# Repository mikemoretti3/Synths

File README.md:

This is my synth design repo.  It includes schematics, board files, and notes for some of the synth designs I've made/borrowed.  Some of these come from Electronotes, MFOS, and elsewhere.  There are also my own designs (under the mordent directory).

The files in this repo were made using Eagle 6.5 (and there is a library file I use in here too).

In general, I prefer flying wire panel component wiring.  I have one pad for GNDPNL which I use to ground all my panel components that need ground.  I connect that pad to one component and then string the rest off each other from there.  Also, make note of pot-pinout.jpg.  That is how I wire pretty much all my pots.  Some of the Electronotes ones may be backward (because I messed up the ordering or they just did it in reverse; I've seen this on VCF frequency/resonance pots from different vendors; some turn clockwise for higher resonance, etc and some turn anti-clockwise).

Don't build VCO1.  I have to look at my module and take a picture and figure out some resistor changes.  I probably shouldn't have included that one yet (I plan to redo that board at some point).

The VEWA can be built as separate modules (this is my preferred way to build it).  There is an LFO board and a filter board.  For the filter board I put jacks in for the 3 frequency CVs  (one for each of the formant filters), the notch, and the Q.  This module is wired for +/-15v.  If you have +/-12 look at the jpg for that.  It's ok to use 100k pots instead of 200k.  There are lines marked A though H, only 5 of which have pads, here is what they mean (ignore the fact that they say "to switches" unless you want to combine the lfo board with it):
C,D,E - are input jacks for freq modulation for the 1st-3rd formant  filters
G - is an input jack for the notch filter frequency CV modulation
H - is an input jack for Q (resonance) CV modulation (Q anim),  (internally it's attached to pin 1 of the Q anim pot, this gets fed into the Q summer which outputs to line B)
There are a total of 7 jacks (in, out, and 5 cv modulation inputs).
You can ignore +15VBB, -15VBB, and GNDBB, they were board to board power  for the LFO board that went with the dual board version and aren't connected.  GNDPNL is the ground I use for all the panel wiring and I run ground wires from panel component to panel component.

Most of the rest of the boards are set to run off +/-12v.  +/-15v should be fine although some of the audio signals may be > +/-5v.

The EchoFX is straight from Music From Outer Space; design notes are there.

The Electronotes ones are documented in the EN pdf files.

Under the "mordent" folder, I have my own drum module design based on some electronotes filters, noise, vcos, and ring modulators.  It's very modular and you can probably stripboard or chop out individual parts of it (i.e. noise + filter + env; vco + env; vco + vco + ringmod).  It's pretty straightforward from the board layout and schematic.  There's also a little mixer and mult board.

There's a util-vco that I use a LOT to test new designs with.  I have 12v and 15v versions of this built that I use as a VCO for input to something or an LFO (it has a huge range).  It's not super accurate, but for using it as a test unit it's perfect.

If you have any questions at all please feel free to contact me via github.

Enjoy!
 
Mike Moretti
http://mordent.com
♩♫♫♩♪♩

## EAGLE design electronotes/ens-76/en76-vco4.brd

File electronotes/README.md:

Electronotes modules
Eurorack and other formats

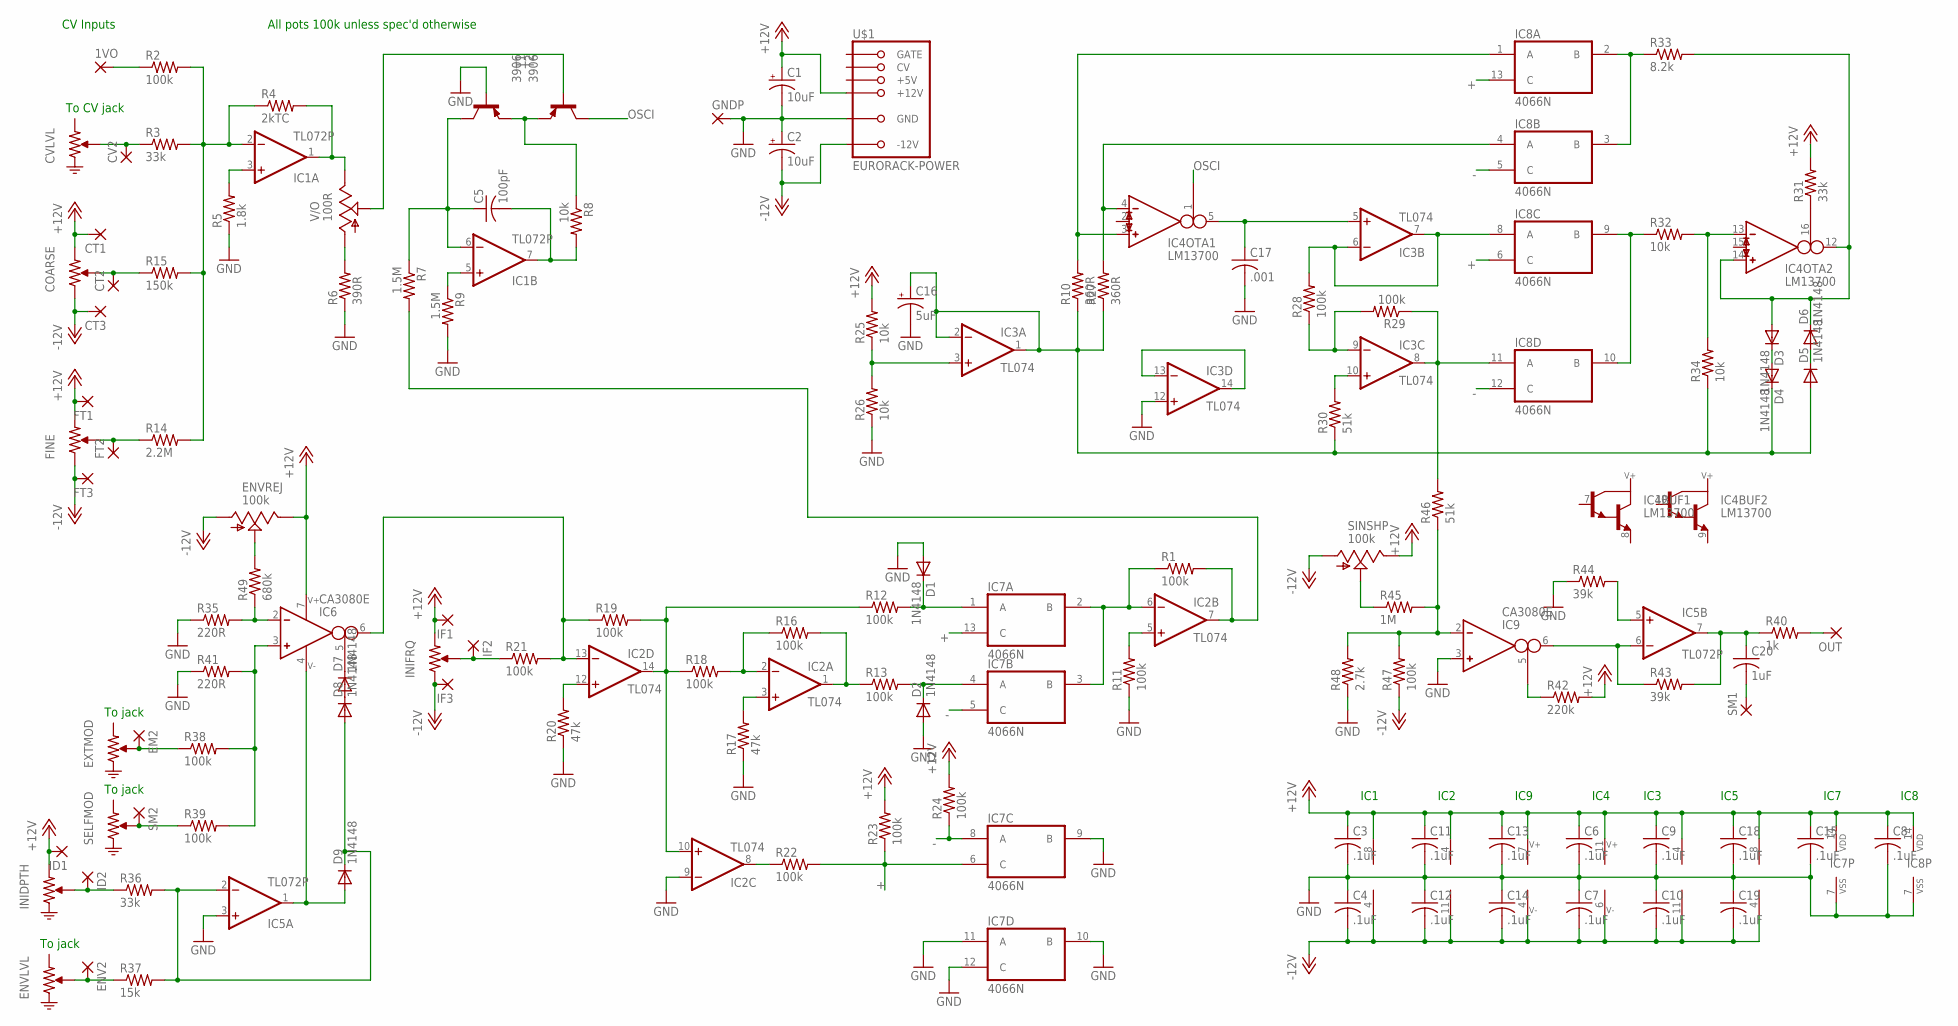
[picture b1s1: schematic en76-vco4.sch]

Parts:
1VO: 2,54/1,0
C1, C2: 10uF; E2-5
C3, C4, C6, C7, C8, C9, C10, C11, C12, C13, C14, C15, C18, C19: .1uF; C050-025X075
C5: 100pF; C050-025X075
C16: 5uF; E2-5
C17: .001; C050-025X075
C20: 1uF; C050-025X075
CT1, CT2, CT3: 2,54/1,0
CV2: 2,54/1,0
D1, D2, D3, D4, D5, D6, D7, D8, D9: 1N4148; DO35-7
EM2: 2,54/1,0
ENV2: 2,54/1,0
ENVREJ: 100k; RJ9W
FT1, FT2, FT3: 2,54/1,0
GNDP: 2,54/1,0
IC1, IC5: TL072P; DIL08
IC2, IC3: TL074; DIL14
IC4: LM13700; DIL16
IC6, IC9: CA3080E; DIL08
IC7, IC8: 4066N; DIL14
ID1, ID2: 2,54/1,0
IF1, IF2, IF3: 2,54/1,0
OUT: 2,54/1,0
R1, R2, R11, R12, R13, R16, R18, R19, R21, R22, R23, R24, R28, R29, R38, R39, R47: 100k; 0207/10
R3, R31, R36: 33k; 0207/10
R4: 2kTC; 0207/10
R5: 1.8k; 0207/10
R6: 390R; 0207/10
R7, R9: 1.5M; 0207/10
R8, R25, R26, R32, R34: 10k; 0207/10
R10, R27: 360R; 0207/10
R14: 2.2M; 0207/10
R15: 150k; 0207/10
R17, R20: 47k; 0207/10
R30, R46: 51k; 0207/10
R33: 8.2k; 0207/10
R35, R41: 220R; 0207/10
R37: 15k; 0207/10
R40: 1k; 0207/10
R42: 220k; 0207/10
R43, R44: 39k; 0207/10
R45: 1M; 0207/10
R48: 2.7k; 0207/10
R49: 680k; 0207/10
SINSHP: 100k; RJ9W
SM1, SM2: 2,54/1,0
T1, T2: 3906; TO92-EBC
U$1: EURORACK-POWER; PINSHRD_PTH_2X8
V/O: 100R; RJ9W

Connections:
+: IC7.6 (C), IC7.13 (C), IC8.6 (C), IC8.13 (C), R22.2, R23.1
+12V: C1.+, C3.1, C6.1, C8.1, C9.1, C11.1, C13.1, C15.1, C18.1, CT1.1, ENVREJ.E, FT1.1, IC1.8 (V+), IC2.4 (V+), IC3.4 (V+), IC4.11 (7), IC5.8 (V+), IC6.7, IC7.14 (VDD), IC8.14 (VDD), IC9.7, ID1.1, IF1.1, R23.2, R24.2, R25.2, R31.2, R42.2, SINSHP.E, U$1.+12V@1 (+12V), U$1.+12V@2 (+12V)
-: IC7.5 (C), IC7.8 (A), IC8.5 (C), IC8.12 (C), R24.1
-12V: C2.-, C4.2, C7.2, C10.2, C12.2, C14.2, C19.2, CT3.1, ENVREJ.A, FT3.1, IC1.4 (V-), IC2.11 (V-), IC3.11 (V-), IC4.6 (4), IC5.4 (V-), IC9.4, IF3.1, R47.1, SINSHP.A, U$1.-12V@1 (-12V), U$1.-12V@2 (-12V)
GND: C1.-, C2.+, C3.2, C4.1, C6.2, C7.1, C8.2, C9.2, C10.1, C11.2, C12.1, C13.2, C14.1, C15.2, C16.-, C17.2, C18.2, C19.1, D1.A, D2.A, GNDP.1, IC2.9 (-IN), IC3.12 (+IN), IC5.3 (+IN), IC7.7 (VSS), IC7.9 (B), IC7.10 (B), IC7.11 (A), IC7.12 (C), IC8.7 (VSS), IC9.3 (IN_P), R5.1, R6.1, R9.2, R11.1, R17.1, R20.1, R26.1, R35.1, R41.1, R44.1, R48.1, T2.B, U$1.GND@1 (GND), U$1.GND@2 (GND), U$1.GND@3 (GND), U$1.GND@4 (GND), U$1.GND@5 (GND), U$1.GND@6 (GND)
unnamed: CT2.1, R15.1
unnamed: CV2.1, R3.1
unnamed: 1VO.1, R2.1
unnamed: T1.B, V/O.S
unnamed: IC1.3 (+IN), R5.2
unnamed: IC1.2 (-IN), R2.2, R3.2, R4.1, R14.2, R15.2
unnamed: IC1.1 (OUT), R4.2, V/O.E
unnamed: R6.2, V/O.A
unnamed: C5.1, IC1.6 (-IN), R7.1, T2.C
unnamed: R8.1, T1.E, T2.E
unnamed: C5.2, IC1.7 (OUT), R8.2
unnamed: FT2.1, R14.1
unnamed: IC4.3 (IN_P), IC8.1 (A), R10.2
unnamed: IC1.5 (+IN), R9.1
unnamed: IC2.6 (-IN), IC7.2 (B), IC7.3 (B), R1.1
unnamed: IC2.5 (+IN), R11.2
unnamed: D1.C, IC7.1 (A), R12.2
unnamed: IC2.10 (+IN), IC2.14 (OUT), R12.1, R18.1, R19.2
unnamed: D2.C, IC7.4 (A), R13.2
unnamed: IC2.1 (OUT), R13.1, R16.2
unnamed: IC2.3 (+IN), R17.2
unnamed: ENVREJ.S, R49.2
unnamed: IC2.13 (-IN), IC6.6 (OUT), R19.1, R21.2
unnamed: IC2.12 (+IN), R20.2
unnamed: IC2.2 (-IN), R16.1, R18.2
unnamed: IC3.8 (OUT), IC8.11 (A), R29.1, R46.2
unnamed: IF2.1, R21.1
unnamed: IC3.3 (+IN), R25.1, R26.2
unnamed: IC2.8 (OUT), R22.1
unnamed: C16.+, D4.C, D5.A, IC3.1 (OUT), IC3.2 (-IN), R10.1, R27.1, R30.1, R34.1
unnamed: IC4.4 (IN_N), IC8.4 (A), R27.2
unnamed: IC8.9 (B), IC8.10 (B), R32.1
unnamed: C17.1, IC3.5 (+IN), IC4.5 (OUT)
unnamed: IC3.6 (-IN), IC3.7 (OUT), IC8.8 (A), R28.2
unnamed: IC3.9 (-IN), R28.1, R29.2
unnamed: IC8.2 (B), IC8.3 (B), R33.1
unnamed: IC3.10 (+IN), R30.2
unnamed: IC4.16 (I_BIAS), R31.1
unnamed: IC4.13 (IN_N), R32.2, R34.2
unnamed: D3.A, D6.C, IC4.12 (OUT), IC4.14 (IN_P), R33.2
unnamed: IC6.2 (IN_N), R35.2, R49.1
unnamed: D3.C, D4.A
unnamed: D5.C, D6.A
unnamed: IC3.13 (-IN), IC3.14 (OUT)
unnamed: D9.A, IC5.1 (OUT), IC6.4
unnamed: D7.C, IC6.5 (I_BIAS)
unnamed: D7.A, D8.C
unnamed: ID2.1, R36.1
unnamed: D8.A, D9.C, IC5.2 (-IN), R36.2, R37.2
unnamed: ENV2.1, R37.1
unnamed: EM2.1, R38.1
unnamed: R39.1, SM2.1
unnamed: C20.1, IC5.7 (OUT), R40.1, R43.2
unnamed: C20.2, SM1.1
unnamed: OUT.1, R40.2
unnamed: IC6.3 (IN_P), R38.2, R39.2, R41.2
unnamed: IC5.6 (-IN), IC9.6 (OUT), R43.1
unnamed: IC9.5 (I_BIAS), R42.1
unnamed: IC5.5 (+IN), R44.2
unnamed: IC9.2 (IN_N), R45.2, R46.1, R47.2, R48.2
unnamed: R45.1, SINSHP.S
unnamed: IC2.7 (OUT), R1.2, R7.2
OSCI: IC4.1 (I_BIAS), T1.C

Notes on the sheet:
All pots 100k unless spec'd otherwise
CV Inputs
IC1
IC2
IC9
IC4
IC3
IC7
IC8
IC5
To CV jack
To jack

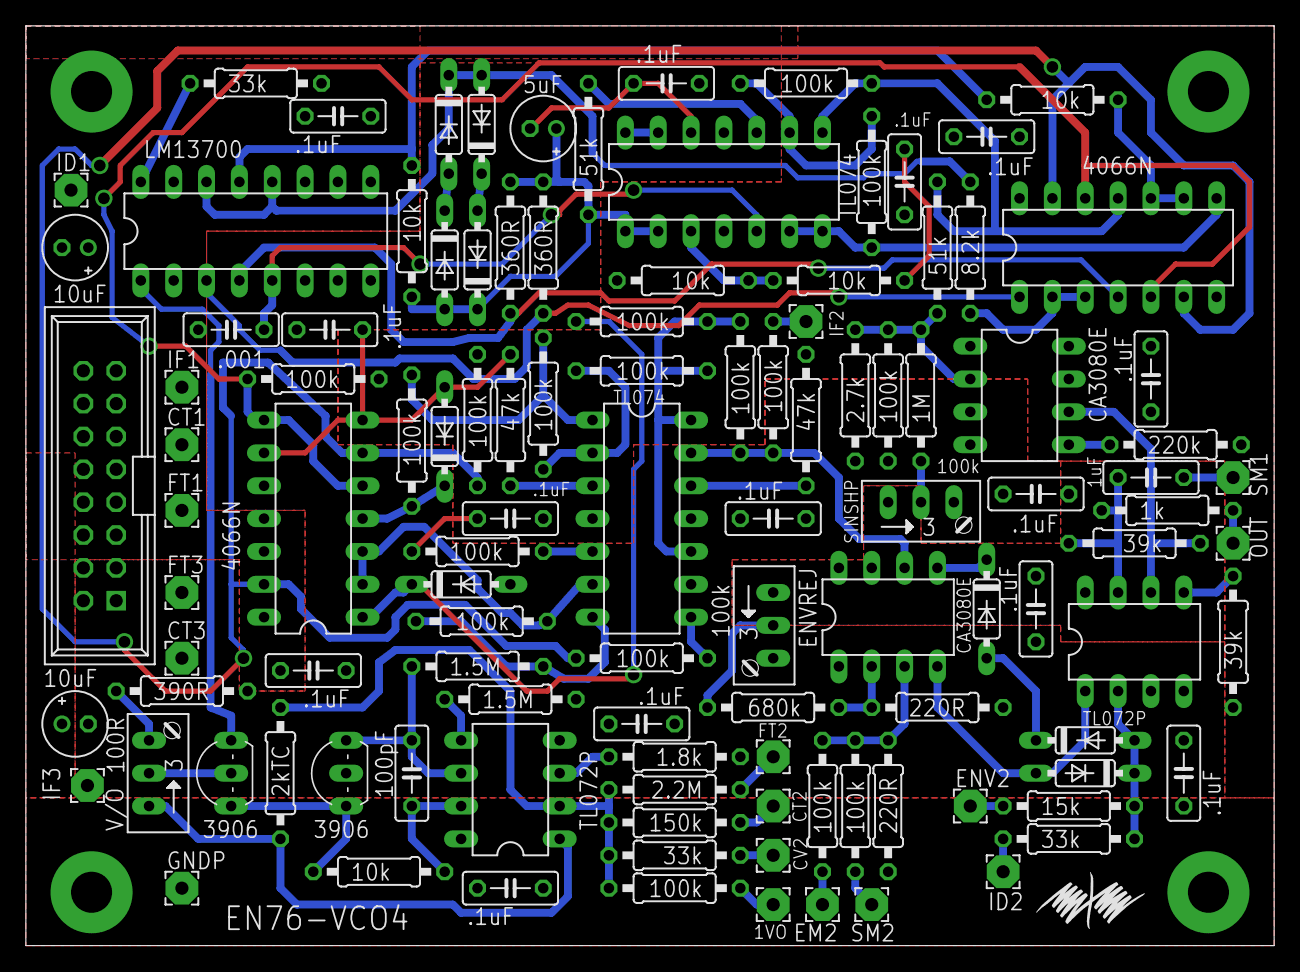
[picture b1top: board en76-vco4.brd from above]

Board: 2 copper layers, 96.5 x 71.1 mm, 112 parts (0 on the bottom side), 68 nets.

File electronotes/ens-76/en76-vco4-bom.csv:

"Part";"Value";"Device";"Package";"Description";"";
"1VO";"";"2,54/1,0";"2,54/1,0";"THROUGH-HOLE PAD";"";
"C1";"10uF";"CPOL-USE2-5";"E2-5";"POLARIZED CAPACITOR, American symbol";"";
"C2";"10uF";"CPOL-USE2-5";"E2-5";"POLARIZED CAPACITOR, American symbol";"";
"C3";".1uF";"C-US050-025X075";"C050-025X075";"CAPACITOR, American symbol";"";
"C4";".1uF";"C-US050-025X075";"C050-025X075";"CAPACITOR, American symbol";"";
"C5";"100pF";"C-US050-025X075";"C050-025X075";"CAPACITOR, American symbol";"";
"C6";".1uF";"C-US050-025X075";"C050-025X075";"CAPACITOR, American symbol";"";
"C7";".1uF";"C-US050-025X075";"C050-025X075";"CAPACITOR, American symbol";"";
"C8";".1uF";"C-US050-025X075";"C050-025X075";"CAPACITOR, American symbol";"";
"C9";".1uF";"C-US050-025X075";"C050-025X075";"CAPACITOR, American symbol";"";
"C10";".1uF";"C-US050-025X075";"C050-025X075";"CAPACITOR, American symbol";"";
"C11";".1uF";"C-US050-025X075";"C050-025X075";"CAPACITOR, American symbol";"";
"C12";".1uF";"C-US050-025X075";"C050-025X075";"CAPACITOR, American symbol";"";
"C13";".1uF";"C-US050-025X075";"C050-025X075";"CAPACITOR, American symbol";"";
"C14";".1uF";"C-US050-025X075";"C050-025X075";"CAPACITOR, American symbol";"";
"C15";".1uF";"C-US050-025X075";"C050-025X075";"CAPACITOR, American symbol";"";
"C16";"5uF";"CPOL-USE2-5";"E2-5";"POLARIZED CAPACITOR, American symbol";"";
"C17";".001";"C-US050-025X075";"C050-025X075";"CAPACITOR, American symbol";"";
"C18";".1uF";"C-US050-025X075";"C050-025X075";"CAPACITOR, American symbol";"";
"C19";".1uF";"C-US050-025X075";"C050-025X075";"CAPACITOR, American symbol";"";
"C20";"1uF";"C-US050-025X075";"C050-025X075";"CAPACITOR, American symbol";"";
"CT1";"";"2,54/1,0";"2,54/1,0";"THROUGH-HOLE PAD";"";
"CT2";"";"2,54/1,0";"2,54/1,0";"THROUGH-HOLE PAD";"";
"CT3";"";"2,54/1,0";"2,54/1,0";"THROUGH-HOLE PAD";"";
"CV2";"";"2,54/1,0";"2,54/1,0";"THROUGH-HOLE PAD";"";
"D1";"1N4148";"1N4148DO35-7";"DO35-7";"DIODE";"";
"D2";"1N4148";"1N4148DO35-7";"DO35-7";"DIODE";"";
"D3";"1N4148";"1N4148DO35-7";"DO35-7";"DIODE";"";
"D4";"1N4148";"1N4148DO35-7";"DO35-7";"DIODE";"";
"D5";"1N4148";"1N4148DO35-7";"DO35-7";"DIODE";"";
"D6";"1N4148";"1N4148DO35-7";"DO35-7";"DIODE";"";
"D7";"1N4148";"1N4148DO35-7";"DO35-7";"DIODE";"";
"D8";"1N4148";"1N4148DO35-7";"DO35-7";"DIODE";"";
"D9";"1N4148";"1N4148DO35-7";"DO35-7";"DIODE";"";
"EM2";"";"2,54/1,0";"2,54/1,0";"THROUGH-HOLE PAD";"";
"ENV2";"";"2,54/1,0";"2,54/1,0";"THROUGH-HOLE PAD";"";
"ENVREJ";"100k";"TRIM_US-RJ9W";"RJ9W";"POTENTIOMETER";"";
"FT1";"";"2,54/1,0";"2,54/1,0";"THROUGH-HOLE PAD";"";
"FT2";"";"2,54/1,0";"2,54/1,0";"THROUGH-HOLE PAD";"";
"FT3";"";"2,54/1,0";"2,54/1,0";"THROUGH-HOLE PAD";"";
"GNDP";"";"2,54/1,0";"2,54/1,0";"THROUGH-HOLE PAD";"";
"IC1";"TL072P";"TL072P";"DIL08";"OP AMP";"";
"IC2";"TL074";"TL074-TOPP";"DIL14";"OP AMP";"";
"IC3";"TL074";"TL074-TOPP";"DIL14";"OP AMP";"";
"IC4";"LM13700";"LM13700-TOPDIP16";"DIL16";"";"";
"IC5";"TL072P";"TL072P";"DIL08";"OP AMP";"";
"IC6";"CA3080E";"CA3080E";"DIL08";"OTA";"";
"IC7";"4066N";"4066N";"DIL14";"Quad bilateral ANALOG SWITCH";"";
"IC8";"4066N";"4066N";"DIL14";"Quad bilateral ANALOG SWITCH";"";
"IC9";"CA3080E";"CA3080E";"DIL08";"OTA";"";
"ID1";"";"2,54/1,0";"2,54/1,0";"THROUGH-HOLE PAD";"";
"ID2";"";"2,54/1,0";"2,54/1,0";"THROUGH-HOLE PAD";"";
"IF1";"";"2,54/1,0";"2,54/1,0";"THROUGH-HOLE PAD";"";
"IF2";"";"2,54/1,0";"2,54/1,0";"THROUGH-HOLE PAD";"";
"IF3";"";"2,54/1,0";"2,54/1,0";"THROUGH-HOLE PAD";"";
"OUT";"";"2,54/1,0";"2,54/1,0";"THROUGH-HOLE PAD";"";
"R1";"100k";"R-US_0207/10";"0207/10";"RESISTOR, American symbol";"";
"R2";"100k";"R-US_0207/10";"0207/10";"RESISTOR, American symbol";"";
"R3";"33k";"R-US_0207/10";"0207/10";"RESISTOR, American symbol";"";
"R4";"2kTC";"R-US_0207/10";"0207/10";"RESISTOR, American symbol";"";
"R5";"1.8k";"R-US_0207/10";"0207/10";"RESISTOR, American symbol";"";
"R6";"390R";"R-US_0207/10";"0207/10";"RESISTOR, American symbol";"";
"R7";"1.5M";"R-US_0207/10";"0207/10";"RESISTOR, American symbol";"";
"R8";"10k";"R-US_0207/10";"0207/10";"RESISTOR, American symbol";"";
"R9";"1.5M";"R-US_0207/10";"0207/10";"RESISTOR, American symbol";"";
"R10";"360R";"R-US_0207/10";"0207/10";"RESISTOR, American symbol";"";
"R11";"100k";"R-US_0207/10";"0207/10";"RESISTOR, American symbol";"";
"R12";"100k";"R-US_0207/10";"0207/10";"RESISTOR, American symbol";"";
"R13";"100k";"R-US_0207/10";"0207/10";"RESISTOR, American symbol";"";
"R14";"2.2M";"R-US_0207/10";"0207/10";"RESISTOR, American symbol";"";
"R15";"150k";"R-US_0207/10";"0207/10";"RESISTOR, American symbol";"";
"R16";"100k";"R-US_0207/10";"0207/10";"RESISTOR, American symbol";"";
"R17";"47k";"R-US_0207/10";"0207/10";"RESISTOR, American symbol";"";
"R18";"100k";"R-US_0207/10";"0207/10";"RESISTOR, American symbol";"";
"R19";"100k";"R-US_0207/10";"0207/10";"RESISTOR, American symbol";"";
"R20";"47k";"R-US_0207/10";"0207/10";"RESISTOR, American symbol";"";
"R21";"100k";"R-US_0207/10";"0207/10";"RESISTOR, American symbol";"";
"R22";"100k";"R-US_0207/10";"0207/10";"RESISTOR, American symbol";"";
"R23";"100k";"R-US_0207/10";"0207/10";"RESISTOR, American symbol";"";
"R24";"100k";"R-US_0207/10";"0207/10";"RESISTOR, American symbol";"";
"R25";"10k";"R-US_0207/10";"0207/10";"RESISTOR, American symbol";"";
"R26";"10k";"R-US_0207/10";"0207/10";"RESISTOR, American symbol";"";
"R27";"360R";"R-US_0207/10";"0207/10";"RESISTOR, American symbol";"";
"R28";"100k";"R-US_0207/10";"0207/10";"RESISTOR, American symbol";"";
"R29";"100k";"R-US_0207/10";"0207/10";"RESISTOR, American symbol";"";
"R30";"51k";"R-US_0207/10";"0207/10";"RESISTOR, American symbol";"";
"R31";"33k";"R-US_0207/10";"0207/10";"RESISTOR, American symbol";"";
"R32";"10k";"R-US_0207/10";"0207/10";"RESISTOR, American symbol";"";
"R33";"8.2k";"R-US_0207/10";"0207/10";"RESISTOR, American symbol";"";
"R34";"10k";"R-US_0207/10";"0207/10";"RESISTOR, American symbol";"";
"R35";"220R";"R-US_0207/10";"0207/10";"RESISTOR, American symbol";"";
"R36";"33k";"R-US_0207/10";"0207/10";"RESISTOR, American symbol";"";
"R37";"15k";"R-US_0207/10";"0207/10";"RESISTOR, American symbol";"";
"R38";"100k";"R-US_0207/10";"0207/10";"RESISTOR, American symbol";"";
"R39";"100k";"R-US_0207/10";"0207/10";"RESISTOR, American symbol";"";
"R40";"1k";"R-US_0207/10";"0207/10";"RESISTOR, American symbol";"";
"R41";"220R";"R-US_0207/10";"0207/10";"RESISTOR, American symbol";"";
"R42";"220k";"R-US_0207/10";"0207/10";"RESISTOR, American symbol";"";
"R43";"39k";"R-US_0207/10";"0207/10";"RESISTOR, American symbol";"";
"R44";"39k";"R-US_0207/10";"0207/10";"RESISTOR, American symbol";"";
"R45";"1M";"R-US_0207/10";"0207/10";"RESISTOR, American symbol";"";
"R46";"51k";"R-US_0207/10";"0207/10";"RESISTOR, American symbol";"";
"R47";"100k";"R-US_0207/10";"0207/10";"RESISTOR, American symbol";"";
"R48";"2.7k";"R-US_0207/10";"0207/10";"RESISTOR, American symbol";"";
"R49";"680k";"R-US_0207/10";"0207/10";"RESISTOR, American symbol";"";
"SINSHP";"100k";"TRIM_US-RJ9W";"RJ9W";"POTENTIOMETER";"";
"SM1";"";"2,54/1,0";"2,54/1,0";"THROUGH-HOLE PAD";"";
"SM2";"";"2,54/1,0";"2,54/1,0";"THROUGH-HOLE PAD";"";
"T1";"3906";"2N3906-PNP-TO92-EBC";"TO92-EBC";"PNP Transistror";"";
"T2";"3906";"2N3906-PNP-TO92-EBC";"TO92-EBC";"PNP Transistror";"";
"U$1";"EURORACK-POWER";"EURORACK-POWER";"PINSHRD_PTH_2X8";"";"";
"V/O";"100R";"TRIM_US-RJ9W";"RJ9W";"POTENTIOMETER";"";

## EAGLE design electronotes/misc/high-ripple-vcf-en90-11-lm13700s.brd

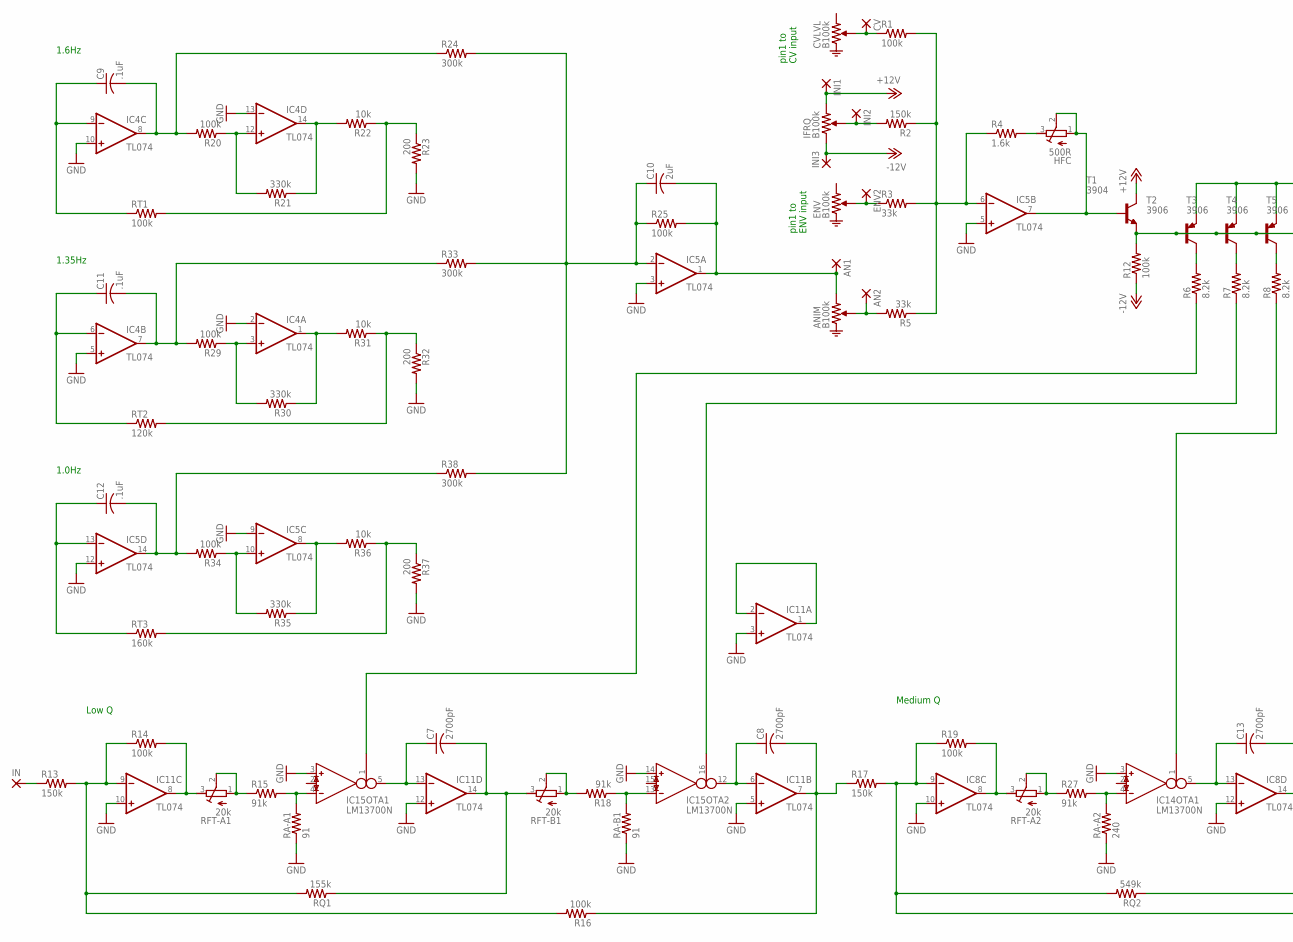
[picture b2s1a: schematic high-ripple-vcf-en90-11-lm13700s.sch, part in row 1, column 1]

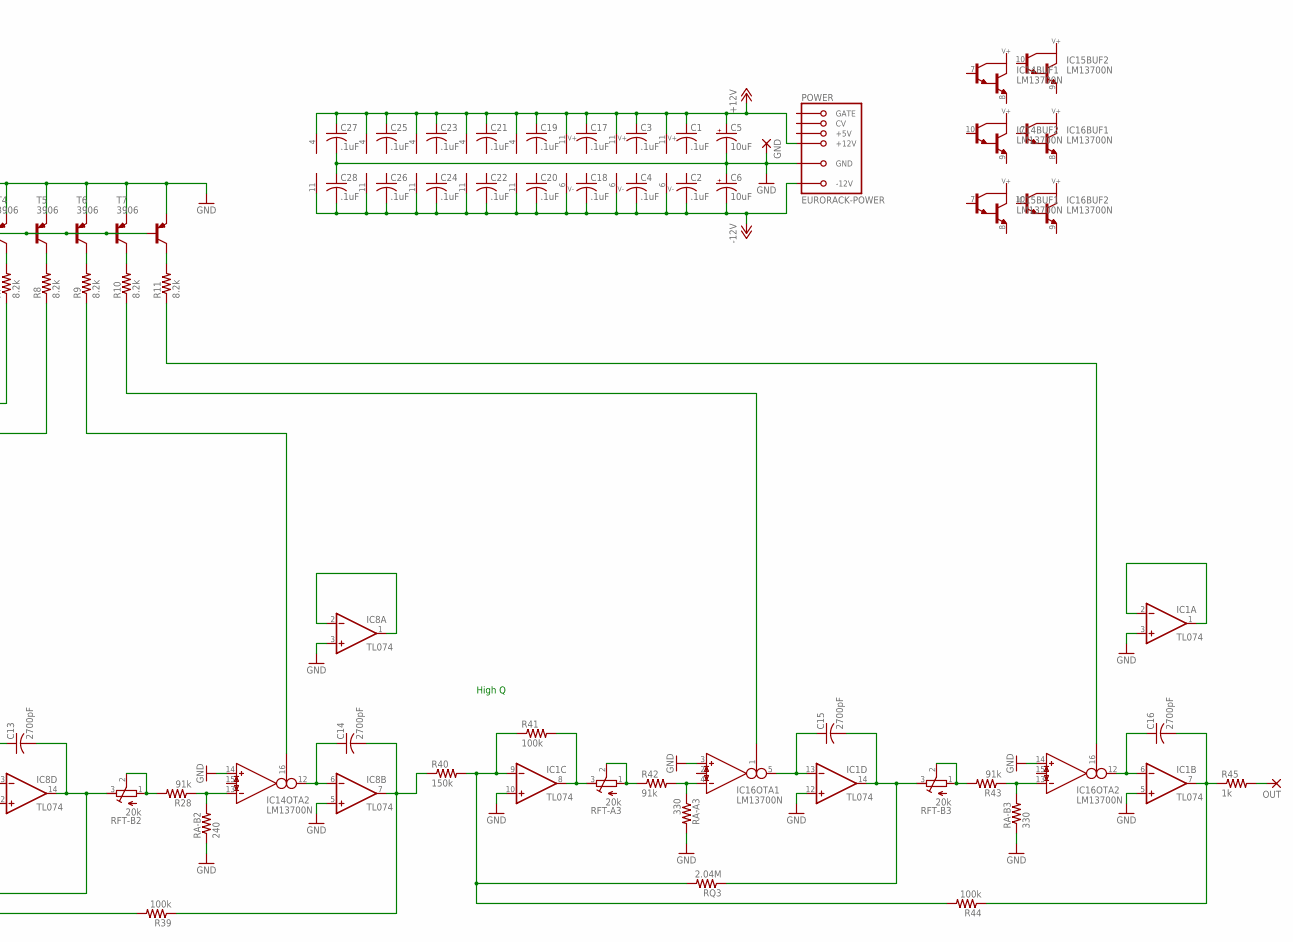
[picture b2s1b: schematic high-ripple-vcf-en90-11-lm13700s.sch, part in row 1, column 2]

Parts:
AN1, AN2: 2,15/1,0
C1, C2, C3, C4, C9, C11, C12, C17, C18, C19, C20, C21, C22, C23, C24, C25, C26, C27, C28: .1uF; C025-025X050
C5, C6: 10uF; E2,5-5
C7, C8, C13, C14, C15, C16: 2700pF; C050-025X075
C10: 2uF; C025-025X050
CV: 2,15/1,0
ENV2: 2,15/1,0
GND: 2,15/1,0
HFC: 500R; RTRIM64W
IC1, IC4, IC5, IC8, IC11: TL074; DIL14
IC14, IC15, IC16: LM13700N; DIL16
IN: 2,15/1,0
INI1, INI2, INI3: 2,15/1,0
OUT: 2,15/1,0
POWER: EURORACK-POWER; PINSHRD_PTH_2X8
R1, R12, R14, R19, R25, R41: 100k; 0207/2V
R2, R17, R40: 150k; 0207/2V
R3, R5: 33k; 0207/2V
R4: 1.6k; 0207/2V
R6, R7, R8, R9, R10, R11: 8.2k; 0207/2V
R13: 150k; 0207/10
R15, R27, R42: 91k; 0207/2V
R16, R20, R29, R34, R39, R44: 100k; 0207/10
R18, R28, R43: 91k; 0207/10
R21, R30, R35: 330k; 0207/2V
R22, R31, R36: 10k; 0207/2V
R23, R32, R37: 200; 0207/2V
R24, R38: 300k; 0207/10
R33: 300k; 0207/2V
R45: 1k; 0207/5V
RA-A1: 91; 0207/2V
RA-A2: 240; 0207/2V
RA-A3: 330; 0207/2V
RA-B1: 91; 0207/2V
RA-B2: 240; 0207/2V
RA-B3: 330; 0207/2V
RFT-A1, RFT-A2, RFT-A3: 20k; RTRIM64W
RFT-B1, RFT-B2, RFT-B3: 20k; RTRIM64W
RQ1: 155k; 0207/10
RQ2: 549k; 0207/10
RQ3: 2.04M; 0207/10
RT1: 100k; 0207/2V
RT2: 120k; 0207/2V
RT3: 160k; 0207/2V
T1: 3904; TO92-EBC
T2, T3, T4, T5, T6, T7: 3906; TO92-EBC

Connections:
+12V: C1.1, C3.1, C5.+, C17.1, C19.1, C21.1, C23.1, C25.1, C27.1, IC1.4 (V+), IC4.4 (V+), IC5.4 (V+), IC8.4 (V+), IC11.4 (V+), IC14.11 (7), IC15.11 (7), IC16.11 (7), INI1.1, POWER.+12V@1 (+12V), POWER.+12V@2 (+12V), T1.C
-12V: C2.2, C4.2, C6.-, C18.2, C20.2, C22.2, C24.2, C26.2, C28.2, IC1.11 (V-), IC4.11 (V-), IC5.11 (V-), IC8.11 (V-), IC11.11 (V-), IC14.6 (4), IC15.6 (4), IC16.6 (4), INI3.1, POWER.-12V@1 (-12V), POWER.-12V@2 (-12V), R12.1
A: IC15.1 (I_BIAS), R6.1
B: IC15.16 (I_BIAS), R7.1
C: IC14.1 (I_BIAS), R8.1
D: IC14.16 (I_BIAS), R9.1
E: IC16.1 (I_BIAS), R10.1
GND: C5.-, C6.+, C27.2, C28.1, GND.1, IC1.3 (+IN), IC1.5 (+IN), IC1.10 (+IN), IC1.12 (+IN), IC4.2 (-IN), IC4.5 (+IN), IC4.10 (+IN), IC4.13 (-IN), IC5.3 (+IN), IC5.5 (+IN), IC5.9 (-IN), IC5.12 (+IN), IC8.3 (+IN), IC8.5 (+IN), IC8.10 (+IN), IC8.12 (+IN), IC11.3 (+IN), IC11.5 (+IN), IC11.10 (+IN), IC11.12 (+IN), IC14.3 (IN_P), IC14.14 (IN_P), IC15.3 (IN_P), IC15.14 (IN_P), IC16.3 (IN_P), IC16.14 (IN_P), POWER.GND@1 (GND), POWER.GND@2 (GND), POWER.GND@3 (GND), POWER.GND@4 (GND), POWER.GND@5 (GND), POWER.GND@6 (GND), R23.2, R32.2, R37.2, RA-A1.1, RA-A2.1, RA-A3.2, RA-B1.1, RA-B2.1, RA-B3.1, T2.E, T3.E, T4.E, T5.E, T6.E, T7.E
unnamed: C10.1, IC5.2 (-IN), R24.2, R25.1, R33.2, R38.2
unnamed: CV.1, R1.1
unnamed: INI2.1, R2.2
unnamed: ENV2.1, R3.1
unnamed: AN2.1, R5.2
unnamed: IC5.6 (-IN), R1.2, R2.1, R3.2, R4.1, R5.1
unnamed: HFC.3 (E), R4.2
unnamed: HFC.1 (A), HFC.2 (S), IC5.7 (OUT), T1.B
unnamed: R12.2, T1.E, T2.B, T3.B, T4.B, T5.B, T6.B, T7.B
unnamed: R6.2, T2.C
unnamed: R7.2, T3.C
unnamed: R8.2, T4.C
unnamed: R9.2, T5.C
unnamed: R10.2, T6.C
unnamed: R11.2, T7.C
unnamed: C9.2, IC4.8 (OUT), R20.2, R24.1
unnamed: IC4.12 (+IN), R20.1, R21.2
unnamed: IC4.14 (OUT), R21.1, R22.2
unnamed: R22.1, R23.1, RT1.2
unnamed: C11.2, IC4.7 (OUT), R29.2, R33.1
unnamed: C9.1, IC4.9 (-IN), RT1.1
unnamed: IC4.3 (+IN), R29.1, R30.2
unnamed: IC4.1 (OUT), R30.1, R31.2
unnamed: R31.1, R32.1, RT2.2
unnamed: C11.1, IC4.6 (-IN), RT2.1
unnamed: C12.2, IC5.14 (OUT), R34.2, R38.1
unnamed: IC5.10 (+IN), R34.1, R35.2
unnamed: IC5.8 (OUT), R35.1, R36.2
unnamed: R36.1, R37.1, RT3.2
unnamed: C12.1, IC5.13 (-IN), RT3.1
unnamed: C8.2, IC11.7 (OUT), R16.1, R17.1
unnamed: IC8.8 (OUT), R19.2, RFT-A2.3 (E)
unnamed: R27.1, RFT-A2.1 (A), RFT-A2.2 (S)
unnamed: IC14.4 (IN_N), R27.2, RA-A2.2
unnamed: C13.1, IC8.13 (-IN), IC14.5 (OUT)
unnamed: IC11.8 (OUT), R14.2, RFT-A1.3 (E)
unnamed: R15.1, RFT-A1.1 (A), RFT-A1.2 (S)
unnamed: IC15.4 (IN_N), R15.2, RA-A1.2
unnamed: C7.1, IC11.13 (-IN), IC15.5 (OUT)
unnamed: C7.2, IC11.14 (OUT), RFT-B1.3 (E), RQ1.1
unnamed: C13.2, IC8.14 (OUT), RFT-B2.3 (E), RQ2.1
unnamed: R18.2, RFT-B1.1 (A), RFT-B1.2 (S)
unnamed: IC15.13 (IN_N), R18.1, RA-B1.2
unnamed: C8.1, IC11.6 (-IN), IC15.12 (OUT)
unnamed: IC11.9 (-IN), R13.2, R14.1, R16.2, RQ1.2
unnamed: IC11.1 (OUT), IC11.2 (-IN)
unnamed: R28.2, RFT-B2.1 (A), RFT-B2.2 (S)
unnamed: IC14.13 (IN_N), R28.1, RA-B2.2
unnamed: C14.1, IC8.6 (-IN), IC14.12 (OUT)
unnamed: IC8.9 (-IN), R17.2, R19.1, R39.2, RQ2.2
unnamed: IC8.1 (OUT), IC8.2 (-IN)
unnamed: C14.2, IC8.7 (OUT), R39.1, R40.1
unnamed: IC1.8 (OUT), R41.2, RFT-A3.3 (E)
unnamed: R42.1, RFT-A3.1 (A), RFT-A3.2 (S)
unnamed: IC16.4 (IN_N), R42.2, RA-A3.1
unnamed: C15.1, IC1.13 (-IN), IC16.5 (OUT)
unnamed: C15.2, IC1.14 (OUT), RFT-B3.3 (E), RQ3.1
unnamed: R43.2, RFT-B3.1 (A), RFT-B3.2 (S)
unnamed: IC16.13 (IN_N), R43.1, RA-B3.2
unnamed: C16.1, IC1.6 (-IN), IC16.12 (OUT)
unnamed: IC1.9 (-IN), R40.2, R41.1, R44.2, RQ3.2
unnamed: IC1.1 (OUT), IC1.2 (-IN)
unnamed: C16.2, IC1.7 (OUT), R44.1, R45.1
unnamed: IN.1, R13.1
unnamed: OUT.1, R45.2
unnamed: IC16.16 (I_BIAS), R11.1
X: AN1.1, C10.2, IC5.1 (OUT), R25.2

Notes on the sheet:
pin1 to ENV input
1.6Hz
1.35Hz
1.0Hz
Low Q
Medium Q
High Q
pin1 to CV input

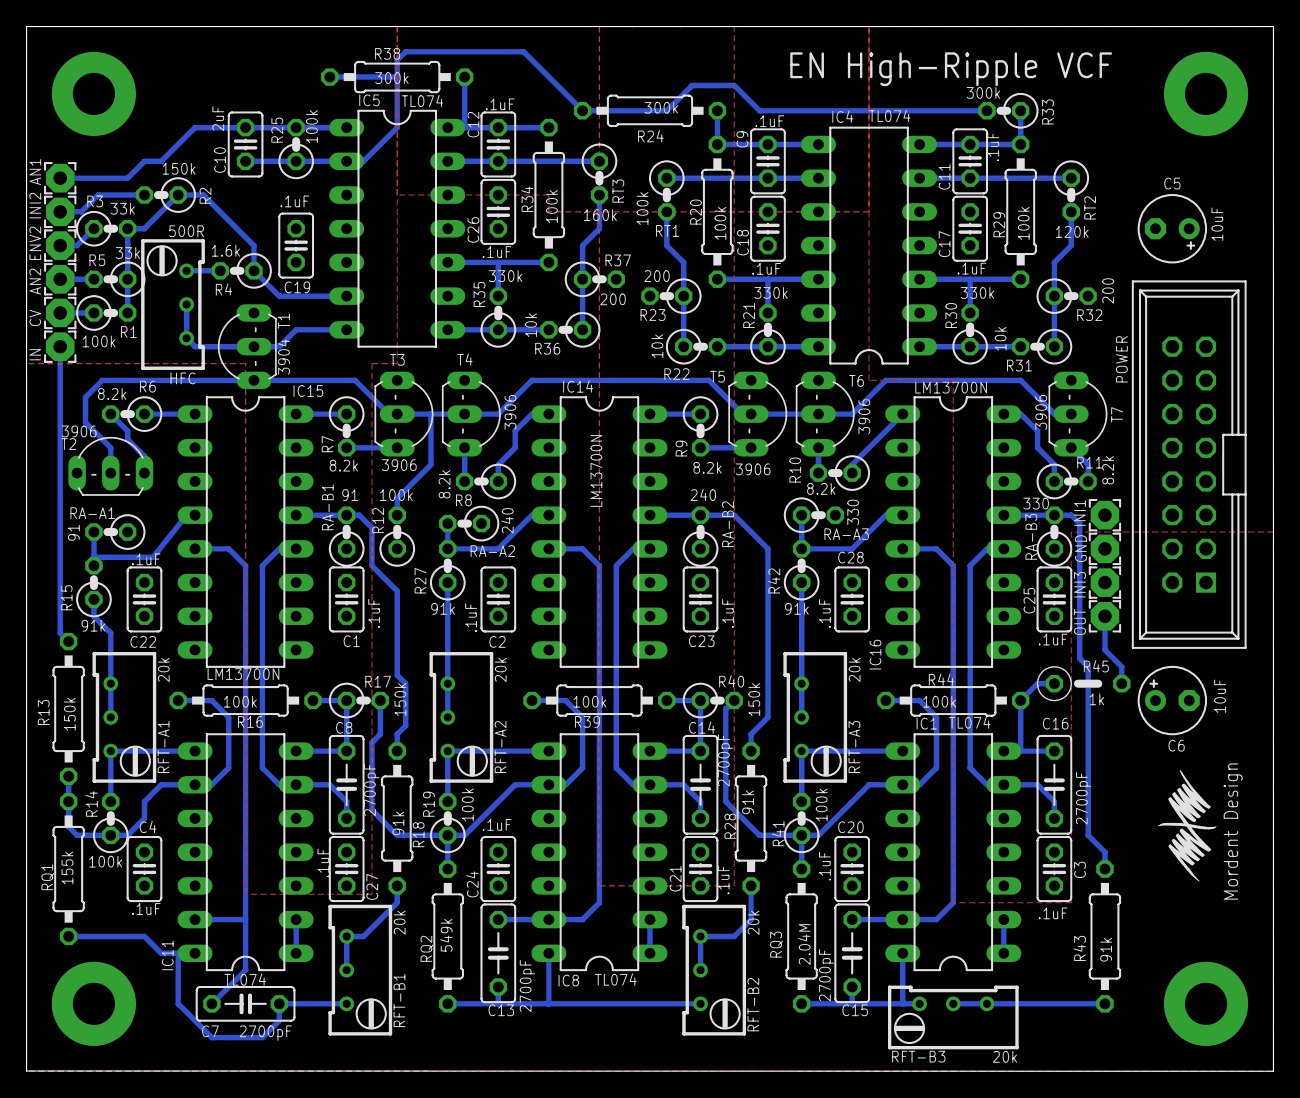
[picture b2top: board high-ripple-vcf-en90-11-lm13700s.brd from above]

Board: 2 copper layers, 94.0 x 78.7 mm, 117 parts (0 on the bottom side), 75 nets.

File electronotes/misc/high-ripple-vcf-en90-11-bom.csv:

Qty,Value,Device,Package,Parts,Description
7,.1uF,C-US050-025X075,C050-025X075,"C1, C2, C3, C4, C9, C11, C12","CAPACITOR, American symbol"
6,2700pF,C-US050-025X075,C050-025X075,"C7, C8, C13, C14, C15, C16","CAPACITOR, American symbol"
1,2uF,C-US050-025X075,C050-025X075,C10,"CAPACITOR, American symbol"
2,10uF,CPOL-USE2.5-5,"E2,5-5","C5, C6","POLARIZED CAPACITOR, American symbol"
2,91,R-US_0207/10,0207/10,"RA-A1, RA-B1","RESISTOR, American symbol"
3,200,R-US_0207/10,0207/10,"R23, R32, R37","RESISTOR, American symbol"
2,240,R-US_0207/10,0207/10,"RA-A2, RA-B2","RESISTOR, American symbol"
2,330,R-US_0207/10,0207/10,"RA-A3, RA-B3","RESISTOR, American symbol"
1,1k,R-US_0207/10,0207/10,R45,"RESISTOR, American symbol"
1,1.6k,R-US_0207/10,0207/10,R4,"RESISTOR, American symbol"
6,8.2k,R-US_0207/10,0207/10,"R6, R7, R8, R9, R10, R11","RESISTOR, American symbol"
3,10k,R-US_0207/10,0207/10,"R22, R31, R36","RESISTOR, American symbol"
6,20k,R-TRIMM64W,RTRIM64W,"RFT-A1, RFT-A2, RFT-A3, RFT-B1, RFT-B2, RFT-B3",Trimm resistor
2,33k,R-US_0207/10,0207/10,"R3, R5","RESISTOR, American symbol"
6,91k,R-US_0207/10,0207/10,"R15, R18, R27, R28, R42, R43","RESISTOR, American symbol"
13,100k,R-US_0207/10,0207/10,"R1, R12, R14, R16, R19, R20, R25, R29, R34, R39, R41, R44, RT1","RESISTOR, American symbol"
1,120k,R-US_0207/10,0207/10,RT2,"RESISTOR, American symbol"
4,150k,R-US_0207/10,0207/10,"R2, R13, R17, R40","RESISTOR, American symbol"
1,155k,R-US_0207/10,0207/10,RQ1,"RESISTOR, American symbol"
1,160k,R-US_0207/10,0207/10,RT3,"RESISTOR, American symbol"
1,2.04M,R-US_0207/10,0207/10,RQ3,"RESISTOR, American symbol"
3,300k,R-US_0207/10,0207/10,"R24, R33, R38","RESISTOR, American symbol"
3,330k,R-US_0207/10,0207/10,"R21, R30, R35","RESISTOR, American symbol"
1,549k,R-US_0207/10,0207/10,RQ2,"RESISTOR, American symbol"
1,3904,2N3904-NPN-TO92-EBC,TO92-EBC,T1,NPN Transistror
6,3906,2N3906-PNP-TO92-EBC,TO92-EBC,"T2, T3, T4, T5, T6, T7",PNP Transistror
1,500,R-TRIMM64W,RTRIM64W,HFC,Trimm resistor
6,CA3080E,CA3080E,DIL08,"IC4, IC5, IC9, IC10, IC12, IC13",OTA
4,TL072,TL072-TOPP,DIL08,"IC2, IC3, IC6, IC7",OP AMP
3,TL074,TL074-TOPP,DIL14,"IC1, IC8, IC11",OP AMP
1,EURORACK-POWER,EURORACK-POWER,PINSHRD_PTH_2X8,POWER,

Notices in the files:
parts and their libraries:
SparkFun-Connectors: Licensing: Creative Commons ShareAlike 4.0 International - https://creativecommons.org/licenses/by-sa/4.0
